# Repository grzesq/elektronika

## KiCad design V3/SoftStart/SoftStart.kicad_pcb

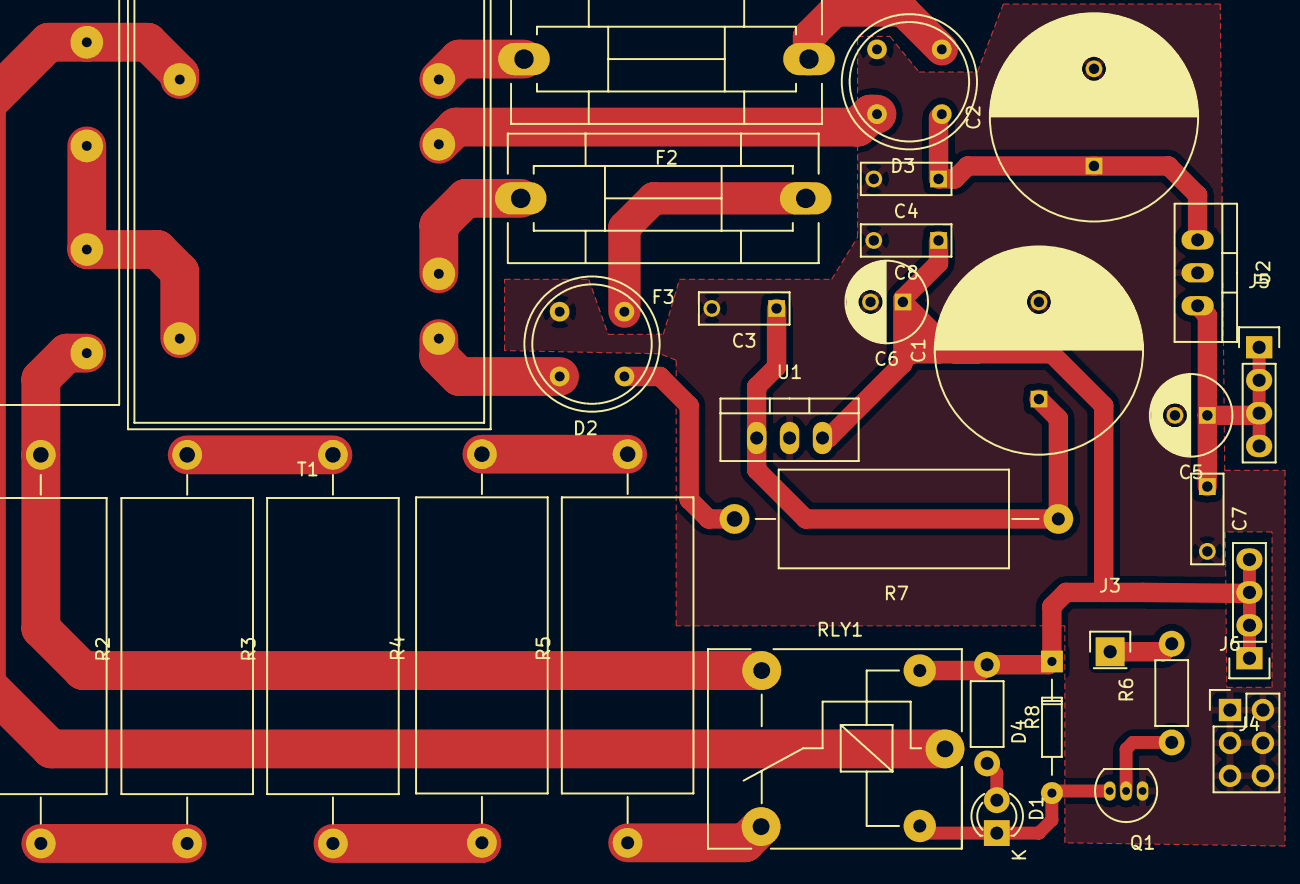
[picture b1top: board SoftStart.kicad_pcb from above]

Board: 2 copper layers, 32 parts (0 on the bottom side), 24 nets.

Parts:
C1, C2: CP; C_Radial_D16_L30_P7.5
C3, C4, C7, C8: C; C_Rect_L7_W2.5_P5
C5, C6: CP; C_Radial_D6.3_L11.2_P2.5
D1: LED; LED-3MM
D2, D3: D_Bridge_-AA+; W10Bridge
D4: D; Diode_DO-35_SOD27_Horizontal_RM10
F2, F3: Fuse; Fuseholder5x20_horiz_SemiClosed_Casing10x25mm
J1: CONN_01X04; 4xSocket
J3: CONN_01X01; Pin_Header_Straight_1x01
J4, J5: CONN_01X04; Pin_Header_Straight_1x04
J6: CONN_02X03; Pin_Header_Straight_2x03
Q1: Q_NPN_BCE; TO-92_Inline_Narrow_Oval
R1, R2, R3, R4, R5: R; Resistor_Horizontal_RM30mm
R6, R8: R; Resistor_Horizontal_RM7mm
R7: R; Resistor_Horizontal_RM25mm
RLY1: RELAY_34.51; Relay_SANYOU_SRD_Series_Form_C
T1: Transformer_1P_2S; TrafoBlock_2x15V
U1: LM7805; TO-220_Neutral123_Vertical
U2: LM7812; TO-220_Neutral123_Vertical

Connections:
GND: C1.2, C2.2, C3.2, C4.2, C5.2, C6.2, C7.2, C8.2, D2.1, D3.1, J6.1, J6.2, J6.3, J6.4, J6.5, J6.6, Q1.1, U1.GND, U2.GND
unnamed: C1.1, C3.1, R7.1, U1.VI
unnamed: C2.1, C4.1, D3.4, U2.VI
unnamed: C5.1, C7.1, J5.1, J5.2, J5.3, J5.4, U2.VO
unnamed: C6.1, C8.1, D4.1, J4.1, J4.2, J4.3, J4.4, R8.1, RLY1.1, U1.VO
unnamed: D1.1, D4.2, Q1.3, RLY1.2
unnamed: D1.2, R8.2
unnamed: D2.2, F3.1
unnamed: D2.3, T1.6
unnamed: D2.4, R7.2
unnamed: D3.2, F2.1
unnamed: D3.3, T1.4
unnamed: F2.2, T1.3
unnamed: F3.2, T1.5
unnamed: J1.1, RLY1.11, T1.1
unnamed: J1.2, J1.3, T1.2
unnamed: J1.4, R1.2, RLY1.14
unnamed: J3.1, R6.2
unnamed: Q1.2, R6.1
unnamed: R1.1, R2.1
unnamed: R2.2, R3.2
unnamed: R3.1, R4.1
unnamed: R4.2, R5.2
unnamed: R5.1, RLY1.12

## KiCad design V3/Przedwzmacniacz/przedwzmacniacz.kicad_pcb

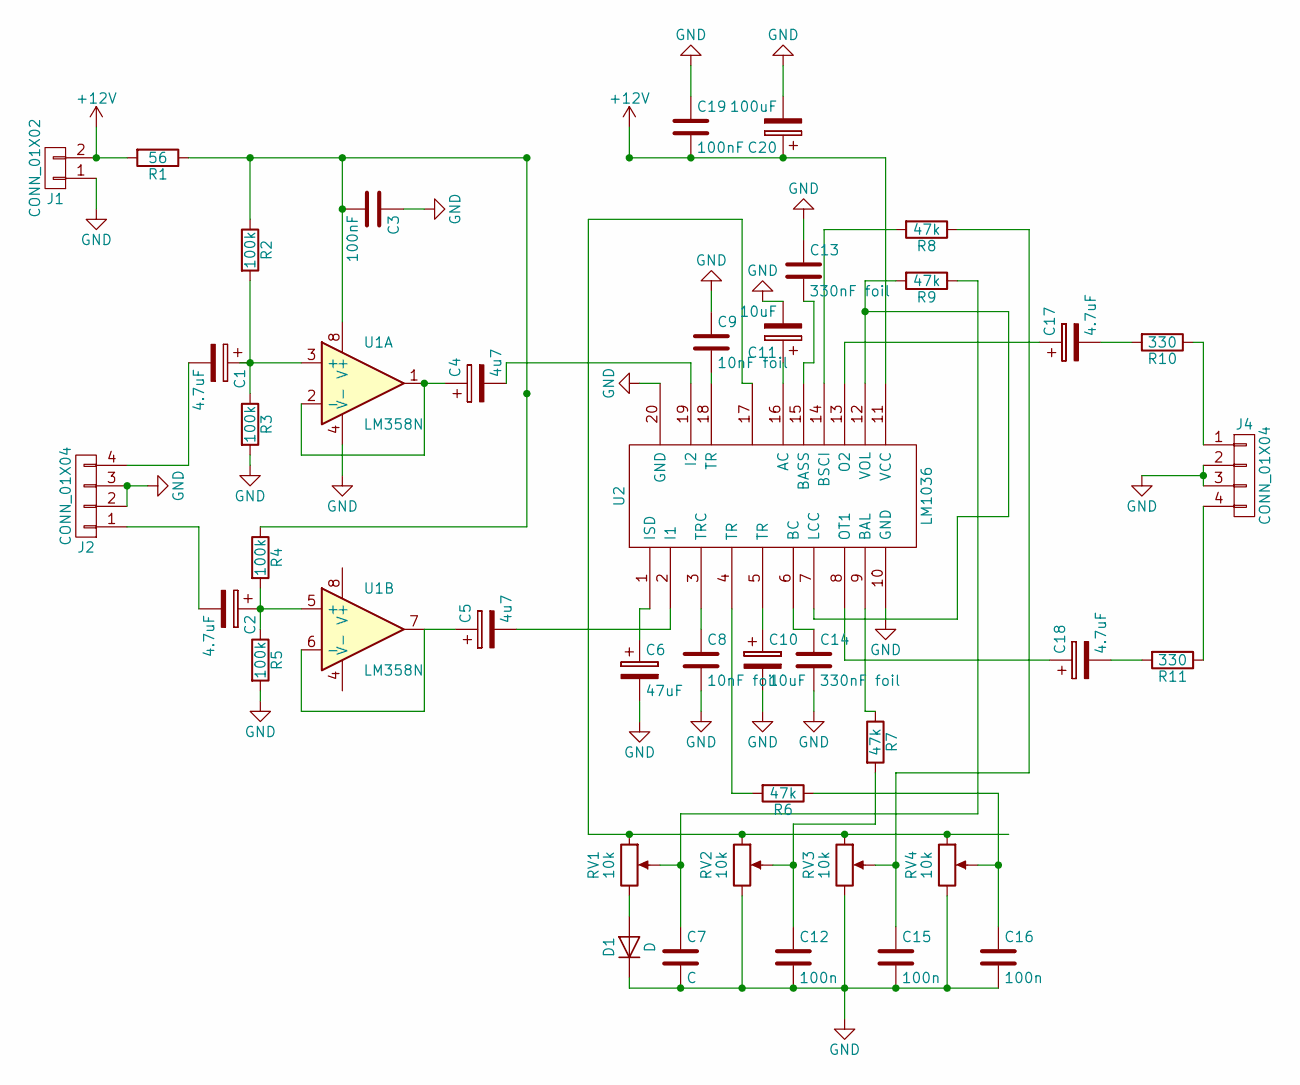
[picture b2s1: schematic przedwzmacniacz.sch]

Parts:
C1, C2, C17, C18: 4.7uF; C_Radial_D5_L11_P2.5
C3, C19: 100nF; C_Rect_L7_W2.5_P5
C4, C5: 4u7; C_Radial_D5_L11_P2.5
C6: 47uF; C_Radial_D5_L11_P2.5
C7: C; C_Rect_L7_W2_P5
C8, C9: 10nF foil; C_Rect_L7_W3.5_P5
C10, C11: 10uF; C_Radial_D5_L11_P2.5
C12, C15, C16: 100n; C_Rect_L7_W2_P5
C13, C14: 330nF foil; C_Rect_L7_W3.5_P5
C20: 100uF; C_Radial_D5_L11_P2.5
D1: D; Diode_DO-35_SOD27_Horizontal_RM10
J1: CONN_01X02; AK300-2
J2, J4: CONN_01X04; AK300-4
R1: 56; Resistor_Horizontal_RM7mm
R2, R3, R4, R5: 100k; Resistor_Horizontal_RM7mm
R6, R7, R8, R9: 47k; Resistor_Horizontal_RM7mm
R10, R11: 330; Resistor_Horizontal_RM7mm
RV1, RV2, RV3, RV4: 10k; Potentiometer_Alps-RK16-single_largePads
U1: LM358N; DIP-8_W7.62mm_LongPads
U2: LM1036; DIP-20_W7.62mm_LongPads

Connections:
+12V: C19.2, C20.1, J1.2, R1.2, U2.11 (VCC)
unnamed: C1.1, R2.2, R3.1, U1.3 (+)
unnamed: C1.2, J2.4
unnamed: C2.1, R4.2, R5.1, U1.5 (+)
unnamed: C2.2, J2.1
unnamed: C3.2, R1.1, R2.1, R4.1, U1.8 (V+)
unnamed: C4.1, U1.1, U1.2 (-)
unnamed: C4.2, U2.19 (I2)
unnamed: C5.1, U1.6 (-), U1.7
unnamed: C5.2, U2.2 (I1)
unnamed: C6.1, U2.1 (ISD)
unnamed: C7.1, R9.1, RV1.2
unnamed: C8.1, U2.3 (TRC)
unnamed: C9.2, U2.18 (TR)
unnamed: C10.1, U2.5 (TR)
unnamed: C11.1, U2.16 (AC)
unnamed: C12.1, R7.2, RV2.2
unnamed: C13.2, U2.15 (BASS)
unnamed: C14.1, U2.6 (BC)
unnamed: C15.1, R8.1, RV3.2
unnamed: C16.1, R6.1, RV4.2
unnamed: C17.1, U2.13 (O2)
unnamed: C17.2, R10.2
unnamed: C18.1, U2.8 (OT1)
unnamed: C18.2, R11.2
unnamed: D1.2 (A), RV1.3
unnamed: J4.1, R10.1
unnamed: J4.4, R11.1
unnamed: R6.2, U2.4 (TR)
unnamed: R7.1, U2.9 (BAL)
unnamed: R8.2, U2.14 (BSCI)
unnamed: RV1.1, RV2.1, RV3.1, RV4.1, U2.17

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
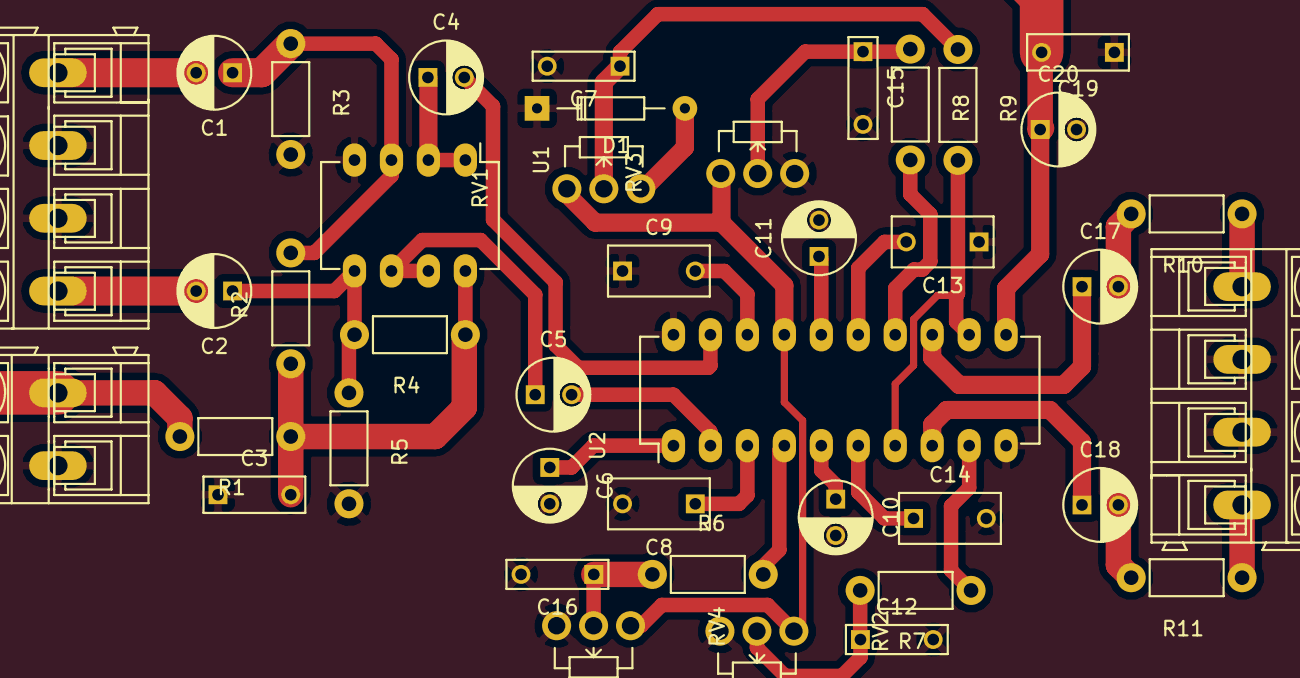
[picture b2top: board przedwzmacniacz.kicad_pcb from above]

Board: 2 copper layers, 41 parts (0 on the bottom side), 34 nets.

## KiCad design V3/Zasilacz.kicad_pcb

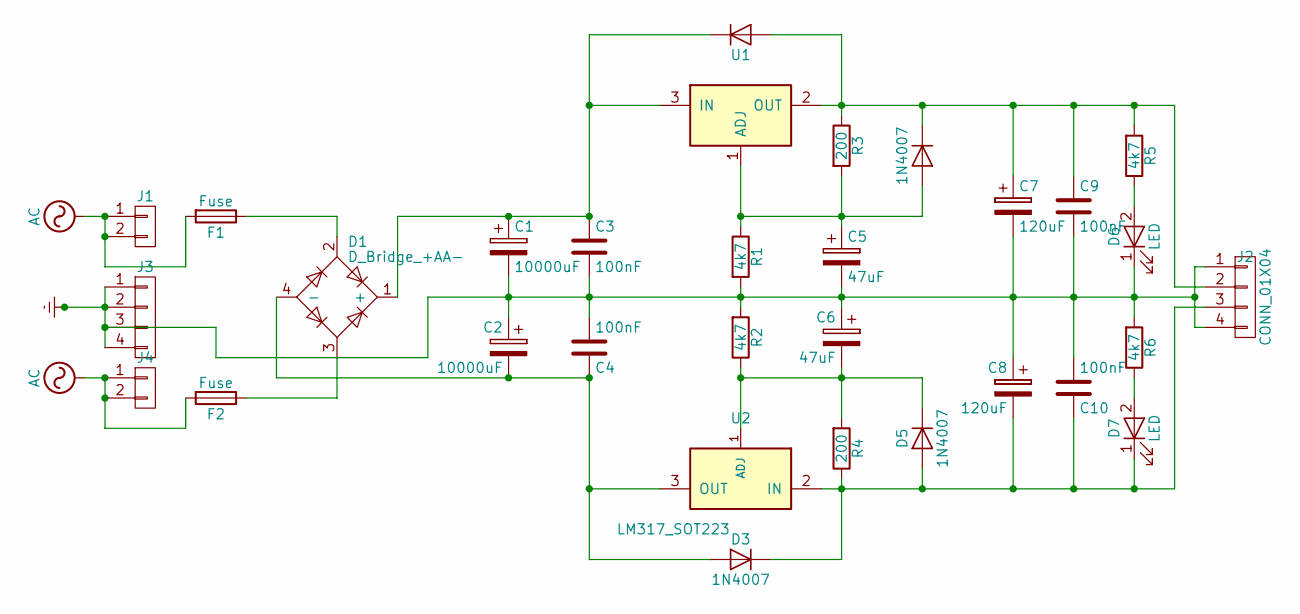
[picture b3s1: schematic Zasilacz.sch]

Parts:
C1, C2: 10000uF; C_Radial_D35_L51_P10
C3, C4, C9, C10: 100nF; C_Rect_L18_W5_P15
C5, C6: 47uF; C_Radial_D5_L11_P2
C7, C8: 120uF; C_Radial_D8_L13_P3.8
D1: D_Bridge_+AA-; Diode_Bridge_30x8X10
D2, D3, D4, D5: 1N4007; Diode_DO-35_SOD27_Horizontal_RM10
D6, D7: LED; LED-5MM
F1, F2: Fuse; Fuseholder5x20_horiz_SemiClosed_Casing10x25mm
J1, J4: CONN_01X02; AK300-2
J2, J3: CONN_01X04; AK300-4
R1, R2, R5, R6: 4k7; Resistor_Horizontal_RM15mm
R3, R4: 200; Resistor_Horizontal_RM15mm
U1, U2: LM317_SOT223; TO-220_Neutral123_Horizontal

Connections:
AC: F1.2, F2.2, J1.1, J1.2, J4.1, J4.2
Earth: C1.2, C2.1, C3.2, C4.2, C5.2, C6.1, C7.2, C8.1, C9.2, C10.2, D6.1 (K), J2.1, J2.4, J3.1, J3.2, J3.3, J3.4, R1.2, R2.2, R6.2
unnamed: C1.1, C3.1, D1.1 (+), D2.1 (K), U1.3 (IN)
unnamed: C2.2, C4.1, D1.4 (-), D3.2 (A), U2.3 (OUT)
unnamed: C5.1, D4.2 (A), R1.1, R3.2, U1.1 (ADJ)
unnamed: C6.2, D5.1 (K), R2.1, R4.2, U2.1 (ADJ)
unnamed: C7.1, C9.1, D2.2 (A), D4.1 (K), J2.2, R3.1, R5.2, U1.2 (OUT)
unnamed: C8.2, C10.1, D3.1 (K), D5.2 (A), D7.1 (K), J2.3, R4.1, U2.2 (IN)
unnamed: D1.2, F1.1
unnamed: D1.3, F2.1
unnamed: D6.2 (A), R5.1
unnamed: D7.2 (A), R6.1

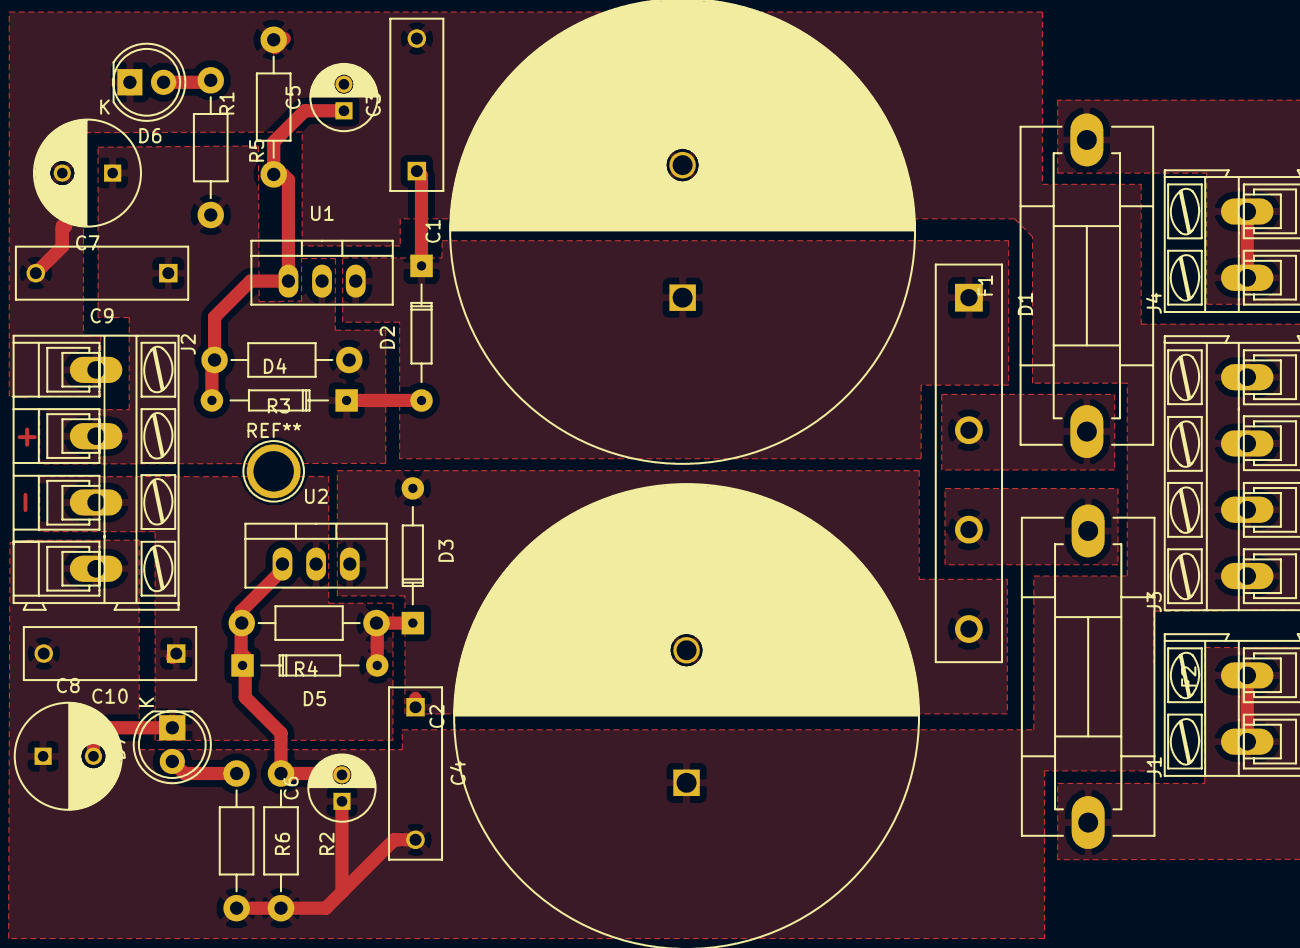
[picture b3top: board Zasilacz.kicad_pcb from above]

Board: 2 copper layers, 31 parts (0 on the bottom side), 12 nets.

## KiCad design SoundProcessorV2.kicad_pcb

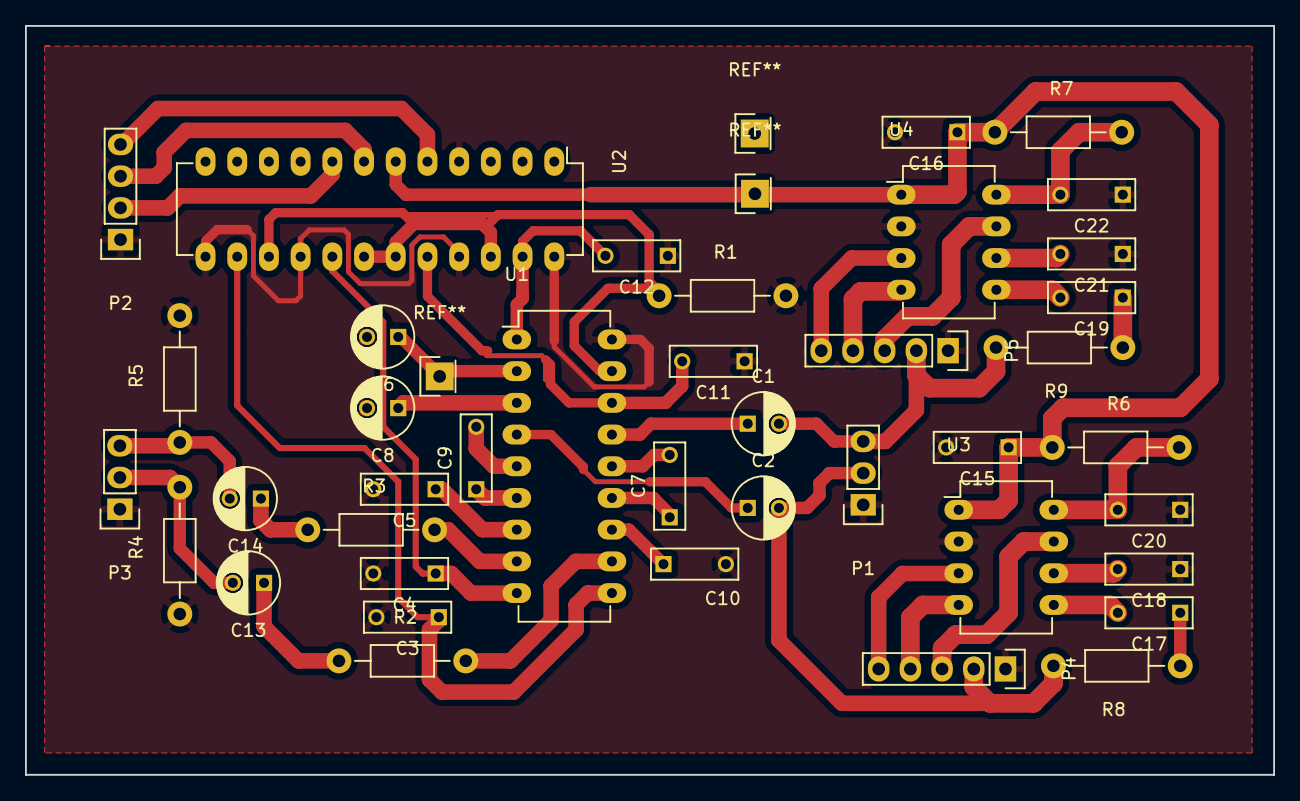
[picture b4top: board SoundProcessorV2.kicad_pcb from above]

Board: 2 copper layers, 100.0 x 60.0 mm, 40 parts (0 on the bottom side), 42 nets.

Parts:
C1, C2, C6: 10uF; C_Radial_D5_L6_P2.5
C3, C4, C11, C12: 100n; C_Rect_L7_W2.5_P5
C5, C10: 15n; C_Rect_L7_W2.5_P5
C7, C9: 56n; C_Rect_L7_W2.5_P5
C8: 100uF; C_Radial_D5_L6_P2.5
C13, C14: 4.7uF; C_Radial_D5_L6_P2.5
C15, C16, C18, C21: 100nF; C_Rect_L7_W2.5_P5
C17, C19: 10nF; C_Rect_L7_W2.5_P5
C20, C22: 33pF; C_Rect_L7_W2.5_P5
P1: CONN_01X04; Pin_Header_Straight_1x03
P2: CONN_01X04; Pin_Header_Straight_1x04
P3: CONN_01X03; Pin_Header_Straight_1x03
P4, P5: CONN_01X05; Pin_Header_Straight_1x05
R1: 2.2k; Resistor_Horizontal_RM10mm
R2, R3: 200; Resistor_Horizontal_RM10mm
R4, R5: 4.7k; Resistor_Horizontal_RM10mm
R6, R7: 200k; Resistor_Horizontal_RM10mm
R8, R9: 22k; Resistor_Horizontal_RM10mm
U1: TDA1524; DIP-18_W7.62mm_LongPads
U2: AD5206; DIP-24_W7.62mm_LongPads
U3, U4: MSGEQ7; DIP-8_W7.62mm_LongPads

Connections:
+5V: C15.1, C16.1, R6.1, R7.1, U2.6, U3.1, U4.1
+12V: C8.1, U1.3
GND: C3.2, C4.2, C5.2, C6.2, C8.2, C10.2, C11.1, C12.1, C15.2, C16.2, C18.1, C20.1, C21.1, C22.1, P1.1, P2.1, P3.1, P4.1, P5.1, R1.2, R4.1, R5.2, U1.18, U2.4, U2.13, U2.16, U2.21, U2.24, U3.2, U4.2
unnamed: C1.1, U1.15
unnamed: C1.2, P1.3, P5.2
unnamed: C2.1, U1.4
unnamed: C2.2, P1.2, P4.2, R8.2
unnamed: C3.1, U1.10, U2.14
unnamed: C4.1, U1.9, U2.17
unnamed: C5.1, U1.7
unnamed: C6.1, U1.2
unnamed: C7.1, U1.13
unnamed: C7.2, U1.14
unnamed: C9.1, U1.6
unnamed: C9.2, U1.5
unnamed: C10.1, U1.12
unnamed: C11.2, U1.16, U2.20
unnamed: C12.2, U1.1, U2.23
unnamed: C13.1, R2.1
unnamed: C13.2, P3.2, R4.2
unnamed: C14.1, R3.1
unnamed: C14.2, P3.3, R5.1
unnamed: C17.1, R8.1
unnamed: C17.2, U3.5
unnamed: C18.2, U3.6
unnamed: C19.1, R9.1
unnamed: C19.2, U4.5
unnamed: C20.2, R6.2, U3.8
unnamed: C21.2, U4.6
unnamed: C22.2, R7.2, U4.8
unnamed: P2.2, U2.8
unnamed: P2.3, U2.7
unnamed: P2.4, U2.5
unnamed: P4.3, U3.7
unnamed: P4.4, U3.4
unnamed: P4.5, U3.3
unnamed: P5.3, U4.7
unnamed: P5.4, U4.4
unnamed: P5.5, U4.3
unnamed: R1.1, U1.17, U2.15, U2.18, U2.19, U2.22
unnamed: R2.2, U1.11
unnamed: R3.2, U1.8

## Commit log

2016-12-28 Sound processor
2017-03-02 Poprawiono zasilanie i wejscie do wizualizera
2017-04-05 Zasilacz v1
2017-04-05 Zasilcz poprawkiw sciezkach
2017-04-23 Przedwzmacniacz
2017-05-21 Added soft start system
2017-05-24 Poprawiony tranzystor
2017-06-27 Wersja finalna
2017-06-29 Zmiana dla radiatorow
